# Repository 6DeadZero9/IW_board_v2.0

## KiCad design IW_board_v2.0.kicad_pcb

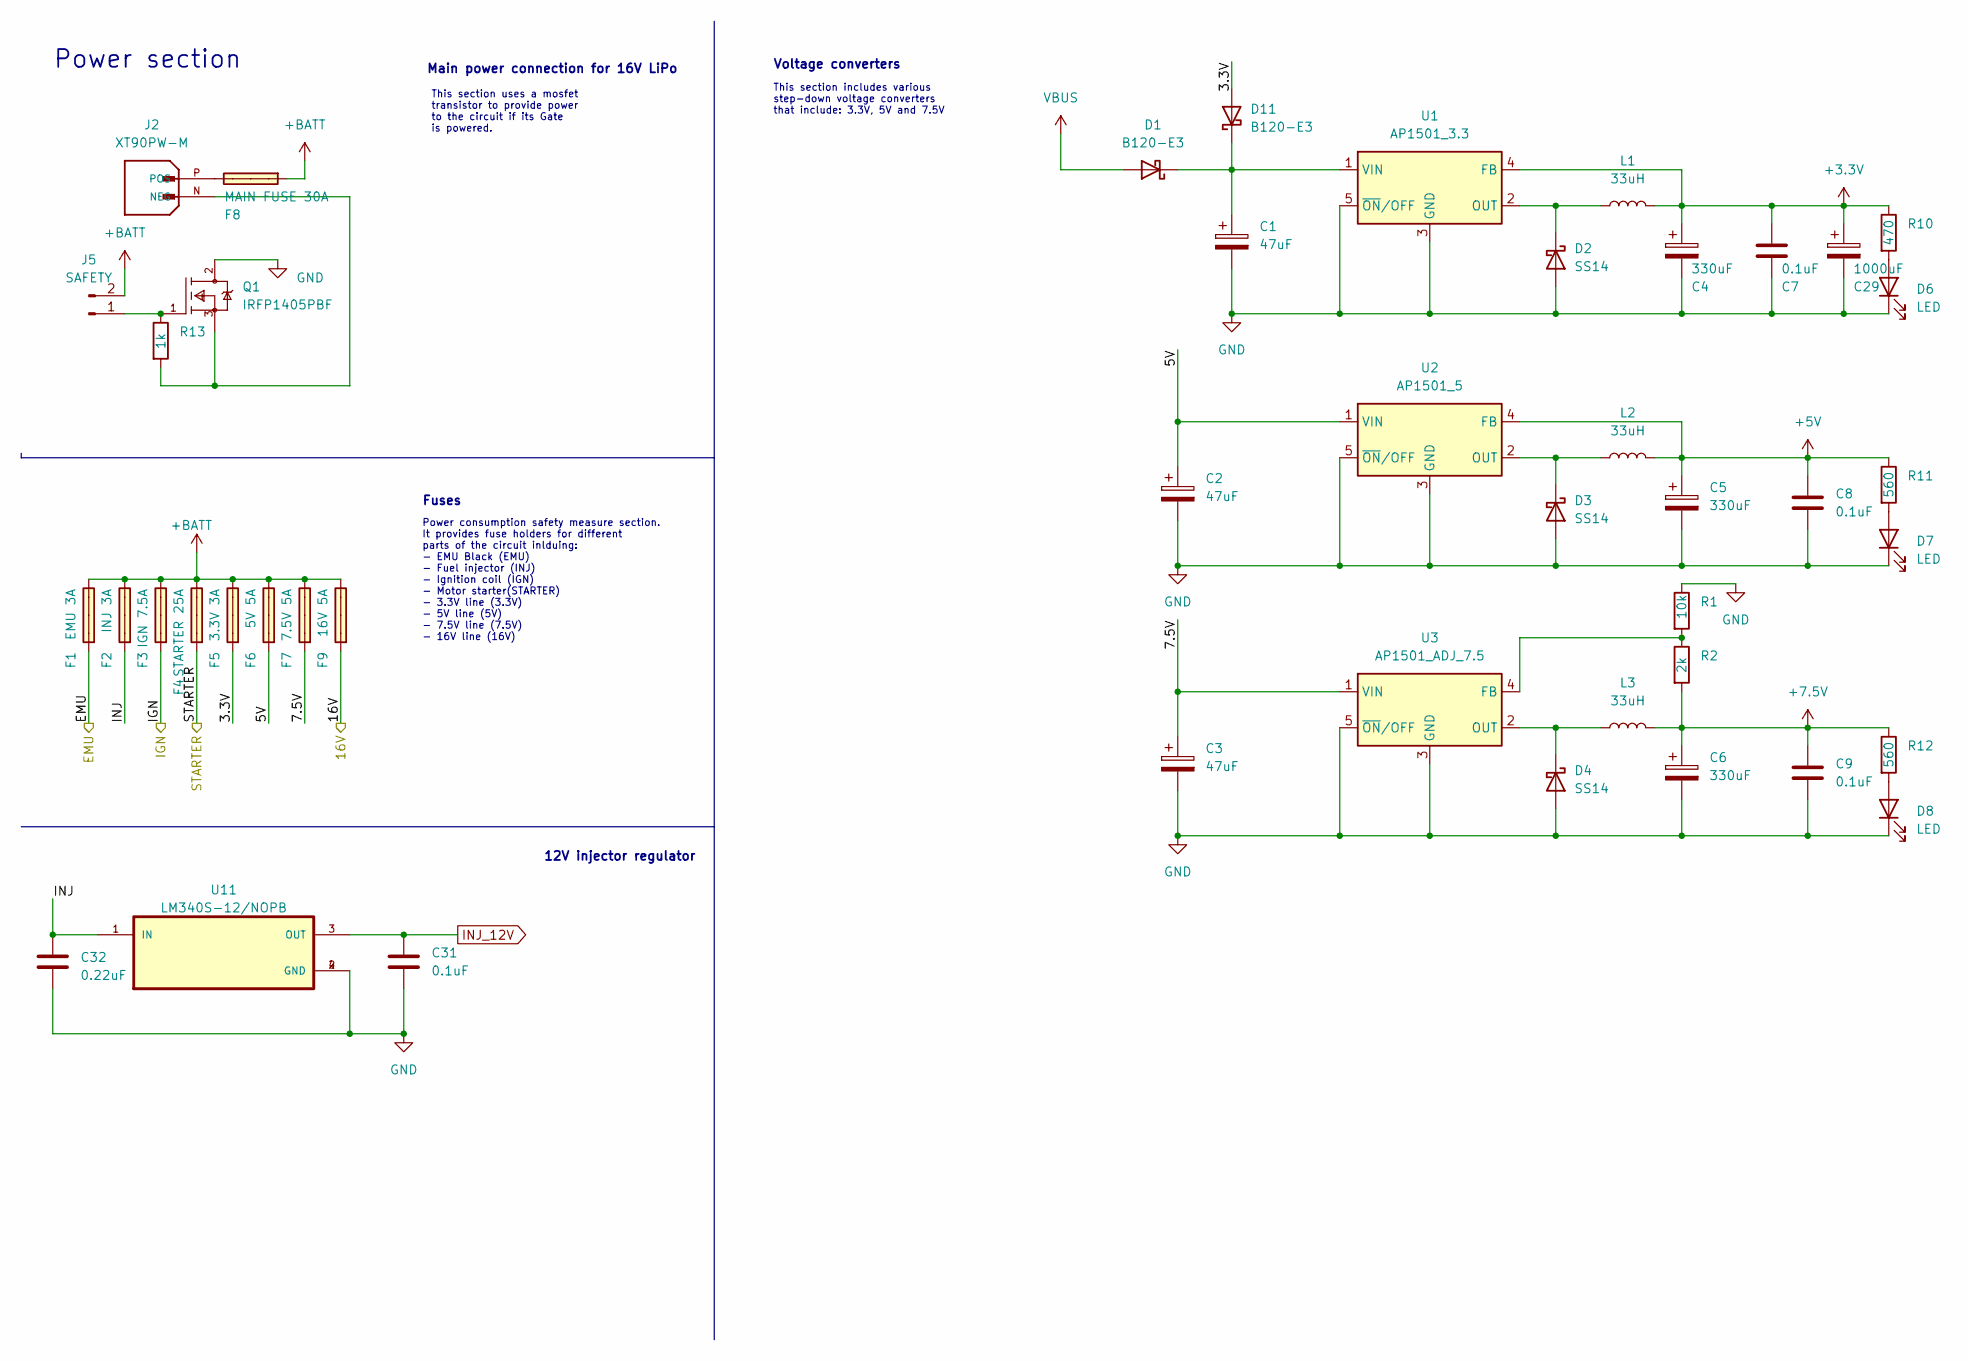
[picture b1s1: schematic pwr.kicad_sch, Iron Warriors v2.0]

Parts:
C1, C2, C3: 47uF; CP_Elec_6.3x5.8
C4, C5, C6: 330uF; CP_Elec_10x10
C7, C8, C9, C31: 0.1uF; C_0603_1608Metric
C29: 1000uF; CP_Radial_D10.0mm_P7.50mm
C32: 0.22uF; C_0603_1608Metric
D1, D11: B120-E3; D_SMA
D2, D3, D4: SS14; D_SMA
D6, D7, D8: LED; LED_0603_1608Metric
F1: EMU 3A; FUSE_3557-2
F2: INJ 3A; FUSE_3557-2
F3: IGN 7.5A; FUSE_3557-2
F4: STARTER 25A; FUSE_3557-2
F5: 3.3V 3A; FUSE_3557-2
F6: 5V 5A; FUSE_3557-2
F7: 7.5V 5A; FUSE_3557-2
F8: MAIN FUSE 30A; FUSE_3557-2
F9: 16V 5A; FUSE_3557-2
J2: XT90PW-M; AMASS_XT90PW-M
J5: SAFETY; TerminalBlock_Phoenix_MPT-0,5-2-2.54_1x02_P2.54mm_Horizontal
L1, L2, L3: 33uH; L_Bourns_SRR1208_12.7x12.7mm
Q1: IRFP1405PBF; TO247AC; mouser part number 942-IRFP1405PBF; digikey description MOSFET N-CH 55V 95A TO247AC
R1: 10k; R_0603_1608Metric
R2: 2k; R_0603_1608Metric
R10: 470; R_0603_1608Metric
R11, R12: 560; R_0603_1608Metric
R13: 1k; R_0603_1608Metric
U1: AP1501_3.3; TO-263-5_TabPin3
U2: AP1501_5; TO-263-5_TabPin3
U3: AP1501_ADJ_7.5; TO-263-5_TabPin3
U11: LM340S-12/NOPB; TO254P1524X483-4N

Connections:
+3.3V: C4.1, C7.1, C29.1, L1.2, R10.1, U1.4 (FB); also elsewhere on the board
+5V: C5.1, C8.1, L2.2, R11.1, U2.4 (FB); also elsewhere on the board
+7.5V: C6.1, C9.1, L3.2, R2.2, R12.1; also elsewhere on the board
+BATT: F1.3, F2.3, F3.3, F4.3, F5.3, F6.3, F7.3, F8.1, F9.3, J5.2
/IO/EMU: F1.1; also elsewhere on the board
/IO/IGN: F3.1; also elsewhere on the board
/IO/STARTER: F4.1; also elsewhere on the board
/PWR/3.3V: D11.2 (A), F5.1
/PWR/5V: C2.1, F6.1, U2.1 (VIN)
/PWR/7.5V: C3.1, F7.1, U3.1 (VIN)
/PWR/16V: F9.1; also elsewhere on the board
/PWR/INJ: C32.1, F2.1, U11.1 (IN)
GND: C1.2, C2.2, C3.2, C4.2, C5.2, C6.2, C7.2, C8.2, C9.2, C29.2, C31.2, C32.2, D2.2 (A), D3.2 (A), D4.2 (A), D6.1 (K), D7.1 (K), D8.1 (K), Q1.2 (D), R1.1, U1.3 (GND), U1.5 (~ON/OFF), U2.3 (GND), U2.5 (~ON/OFF), U3.3 (GND), U3.5 (~ON/OFF), U11.2 (GND), U11.4 (GND); also elsewhere on the board
INJ_12V: C31.1, U11.3 (OUT); also elsewhere on the board
unnamed: C1.1, D1.1 (K), D11.1 (K), U1.1 (VIN)
unnamed: D2.1 (K), L1.1, U1.2 (OUT)
unnamed: D3.1 (K), L2.1, U2.2 (OUT)
unnamed: D4.1 (K), L3.1, U3.2 (OUT)
unnamed: D6.2 (A), R10.2
unnamed: D7.2 (A), R11.2
unnamed: D8.2 (A), R12.2
unnamed: J2.N (NEG), Q1.3 (S), R13.2
unnamed: F8.3, J2.P (POS)
unnamed: J5.1, Q1.1 (G), R13.1
unnamed: R1.2, R2.1, U3.4 (FB)
VBUS: D1.2 (A); also elsewhere on the board

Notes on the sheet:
This section includes various step-down voltage converters that include: 3.3V, 5V and 7.5V
Power consumption safety measure section. It provides fuse holders for different parts of the circuit inlduing: - EMU Black (EMU) - Fuel injector (INJ) - Ignition coil (IGN) - Motor starter(STARTER) - 3.3V line (3.3V) - 5V line (5V) - 7.5V line (7.5V) - 16V line (16V)
This section uses a mosfet transistor to provide power to the circuit if its Gate is powered.
Power section
12V injector regulator
Main power connection for 16V LiPo
Fuses
Voltage converters

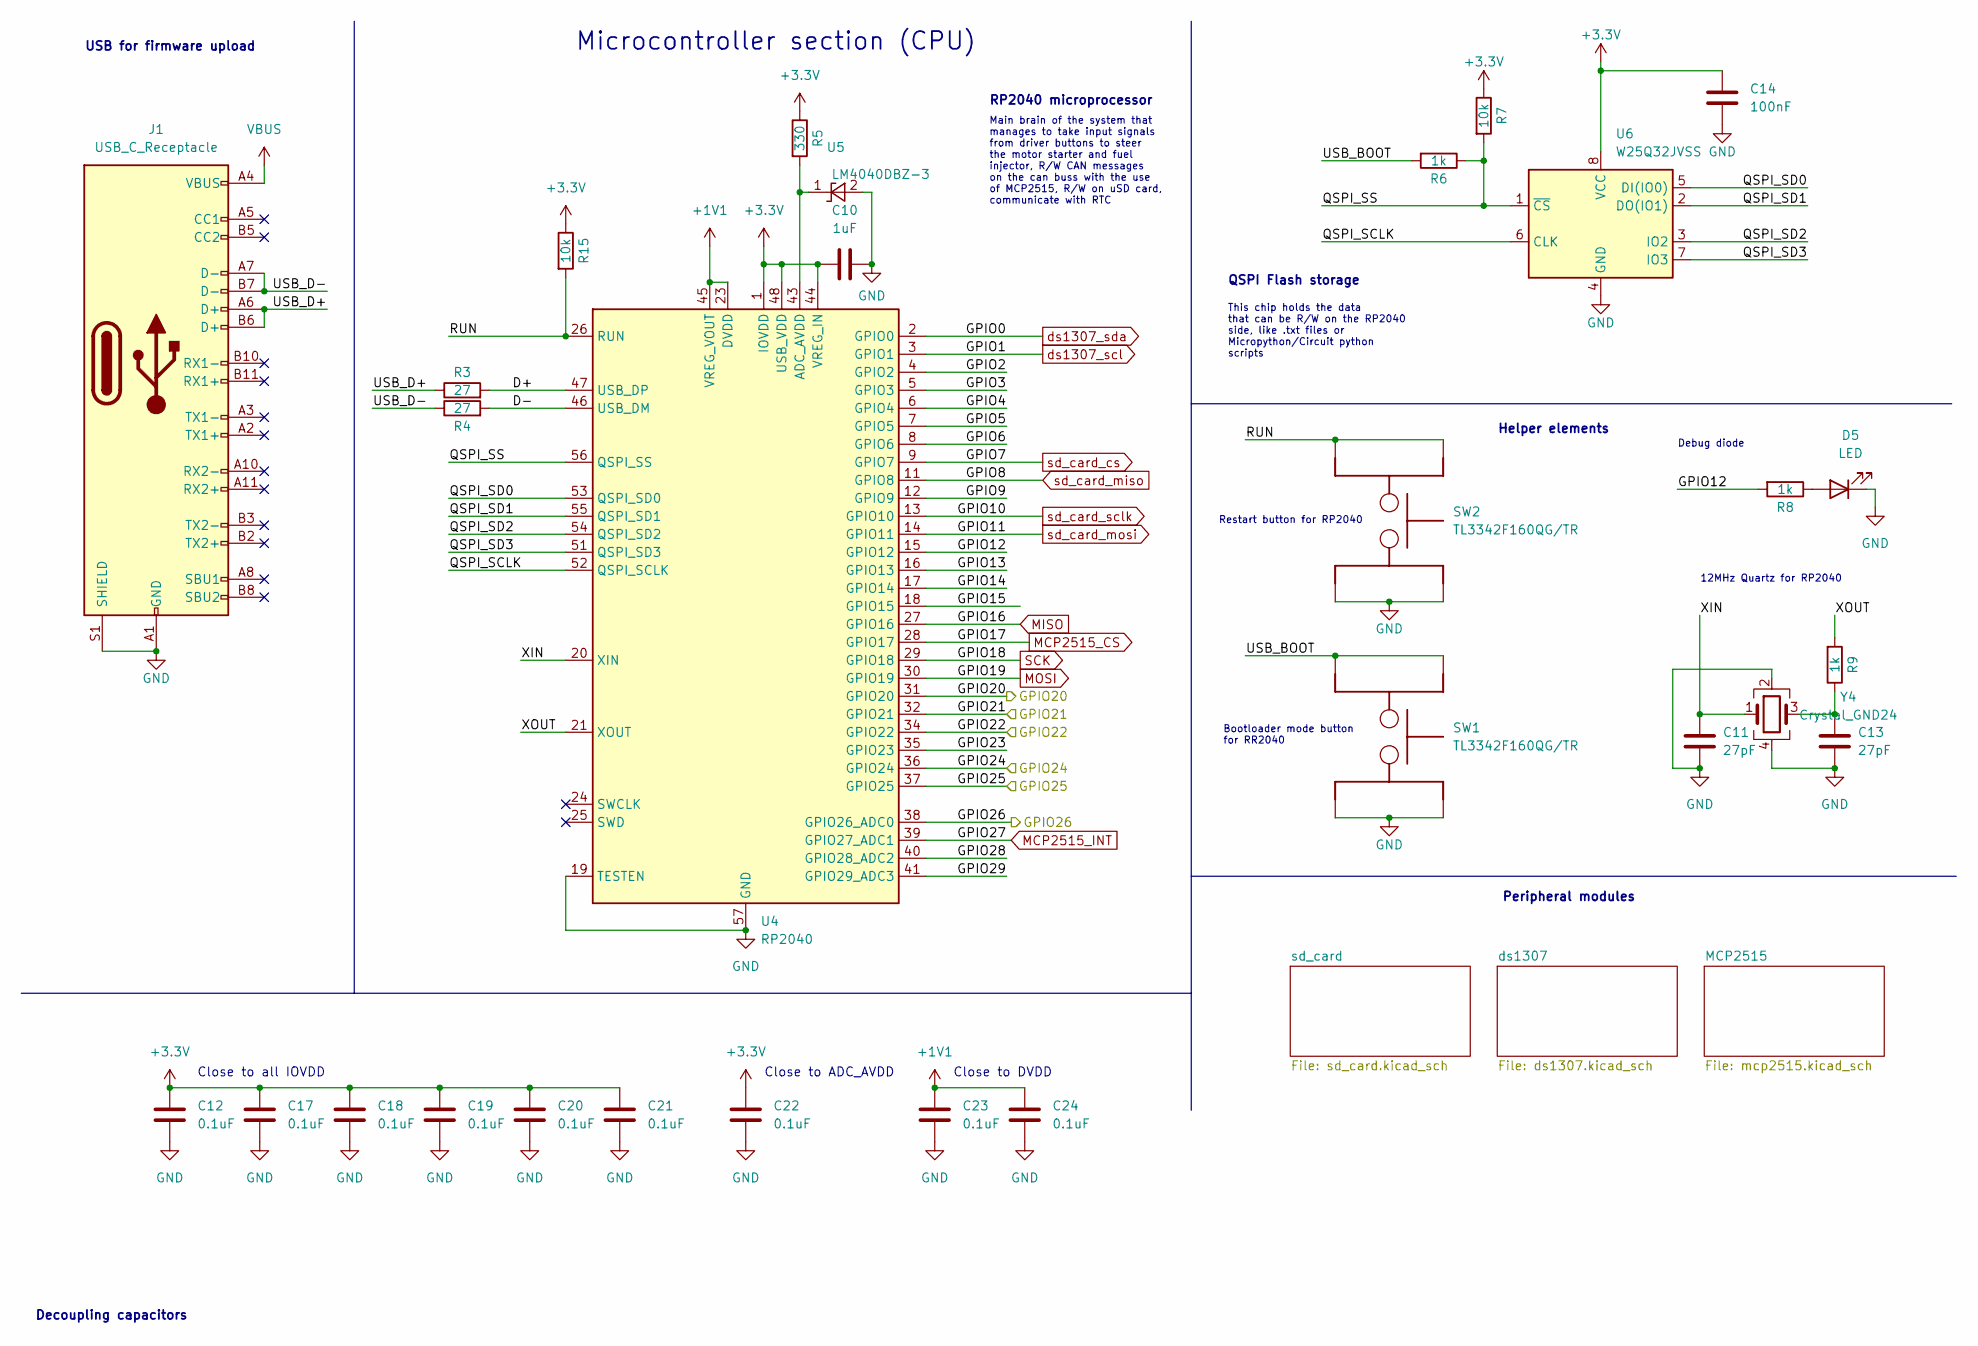
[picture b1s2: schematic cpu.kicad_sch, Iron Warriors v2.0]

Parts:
C10: 1uF; C_0603_1608Metric
C11, C13: 27pF; C_0603_1608Metric
C12, C17, C18, C19, C20, C21, C22, C23, C24: 0.1uF; C_0603_1608Metric
C14: 100nF; C_0603_1608Metric
D5: LED; LED_0603_1608Metric
J1: USB_C_Receptacle; USB_C_Receptacle_HRO_TYPE-C-31-M-12
R3, R4: 27; R_0603_1608Metric
R5: 330; R_0603_1608Metric
R6, R8, R9: 1k; R_0603_1608Metric
R7, R15: 10k; R_0603_1608Metric
SW1, SW2: TL3342F160QG/TR; SW_TL3342F160QG%2fTR
U4: RP2040; QFN-56-1EP_7x7mm_P0.4mm_EP3.2x3.2mm
U5: LM4040DBZ-3; SOT-23
U6: W25Q32JVSS; SOIC-8_5.23x5.23mm_P1.27mm
Y4: Crystal_GND24

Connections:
+1V1: C23.1, C24.1, U4.23 (DVDD), U4.45 (VREG_VOUT), U4.50 (DVDD)
+3.3V: C10.2, C12.1, C14.1, C17.1, C18.1, C19.1, C20.1, C21.1, C22.1, R5.1, R7.1, R15.1, U4.1 (IOVDD), U4.10 (IOVDD), U4.22 (IOVDD), U4.33 (IOVDD), U4.42 (IOVDD), U4.44 (VREG_IN), U4.48 (USB_VDD), U4.49 (IOVDD), U6.8 (VCC); also elsewhere on the board
/CPU/D+: R3.2, U4.47 (USB_DP)
/CPU/D-: R4.2, U4.46 (USB_DM)
/CPU/GPIO2: U4.4 (GPIO2)
/CPU/GPIO3: U4.5 (GPIO3)
/CPU/GPIO4: U4.6 (GPIO4)
/CPU/GPIO5: U4.7 (GPIO5)
/CPU/GPIO6: U4.8 (GPIO6)
/CPU/GPIO9: U4.12 (GPIO9)
/CPU/GPIO12: R8.2, U4.15 (GPIO12)
/CPU/GPIO13: U4.16 (GPIO13)
/CPU/GPIO14: U4.17 (GPIO14)
/CPU/GPIO15: U4.18 (GPIO15)
/CPU/GPIO20: U4.31 (GPIO20); also elsewhere on the board
/CPU/GPIO21: U4.32 (GPIO21); also elsewhere on the board
/CPU/GPIO22: U4.34 (GPIO22); also elsewhere on the board
/CPU/GPIO23: U4.35 (GPIO23)
/CPU/GPIO24: U4.36 (GPIO24); also elsewhere on the board
/CPU/GPIO25: U4.37 (GPIO25); also elsewhere on the board
/CPU/GPIO26: U4.38 (GPIO26_ADC0); also elsewhere on the board
/CPU/GPIO28: U4.40 (GPIO28_ADC2)
/CPU/GPIO29: U4.41 (GPIO29_ADC3)
/CPU/QSPI_SCLK: U4.52 (QSPI_SCLK), U6.6 (CLK)
/CPU/QSPI_SD0: U4.53 (QSPI_SD0), U6.5 (DI(IO0))
/CPU/QSPI_SD1: U4.55 (QSPI_SD1), U6.2 (DO(IO1))
/CPU/QSPI_SD2: U4.54 (QSPI_SD2), U6.3 (IO2)
/CPU/QSPI_SD3: U4.51 (QSPI_SD3), U6.7 (IO3)
/CPU/QSPI_SS: R6.1, R7.2, U4.56 (QSPI_SS), U6.1 (~CS)
/CPU/RUN: R15.2, SW2.3, SW2.4, U4.26 (RUN)
/CPU/USB_BOOT: R6.2, SW1.3, SW1.4
/CPU/USB_D+: J1.A6 (D+), J1.B6 (D+), R3.1
/CPU/USB_D-: J1.A7 (D-), J1.B7 (D-), R4.1
/CPU/XOUT: R9.2, U4.21 (XOUT)
GND: C10.1, C11.2, C12.2, C13.2, C14.2, C17.2, C18.2, C19.2, C20.2, C21.2, C22.2, C23.2, C24.2, D5.1 (K), J1.A1 (GND), J1.A12 (GND), J1.B1 (GND), J1.B12 (GND), J1.S1 (SHIELD), SW1.1, SW1.2, SW2.1, SW2.2, U4.19 (TESTEN), U4.57 (GND), U5.2 (A), U6.4 (GND), Y4.2, Y4.4; also elsewhere on the board
MCP2515_CS: U4.28 (GPIO17); also elsewhere on the board
MCP2515_INT: U4.39 (GPIO27_ADC1); also elsewhere on the board
MISO: U4.27 (GPIO16); also elsewhere on the board
MOSI: U4.30 (GPIO19); also elsewhere on the board
unnamed: D5.2 (A), R8.1
unnamed: R5.2, U4.43 (ADC_AVDD), U5.1 (K)
SCK: U4.29 (GPIO18); also elsewhere on the board
VBUS: J1.A4 (VBUS), J1.A9 (VBUS), J1.B4 (VBUS), J1.B9 (VBUS); also elsewhere on the board
ds1307_scl: U4.3 (GPIO1); also elsewhere on the board
ds1307_sda: U4.2 (GPIO0); also elsewhere on the board
sd_card_cs: U4.9 (GPIO7); also elsewhere on the board
sd_card_miso: U4.11 (GPIO8); also elsewhere on the board
sd_card_mosi: U4.14 (GPIO11); also elsewhere on the board
sd_card_sclk: U4.13 (GPIO10); also elsewhere on the board

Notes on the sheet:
Peripheral modules
Bootloader mode button for RR2040
RP2040 microprocessor
This chip holds the data that can be R/W on the RP2040 side, like .txt files or Micropython/Circuit python scripts
Close to DVDD
Close to all IOVDD
Close to ADC_AVDD
Debug diode
Decoupling capacitors
Restart button for RP2040
USB for firmware upload
Microcontroller section (CPU)
Helper elements
QSPI Flash storage
Main brain of the system that manages to take input signals from driver buttons to steer the motor starter and fuel injector, R/W CAN messages on the can buss with the use of MCP2515, R/W on uSD card, communicate with RTC
12MHz Quartz for RP2040

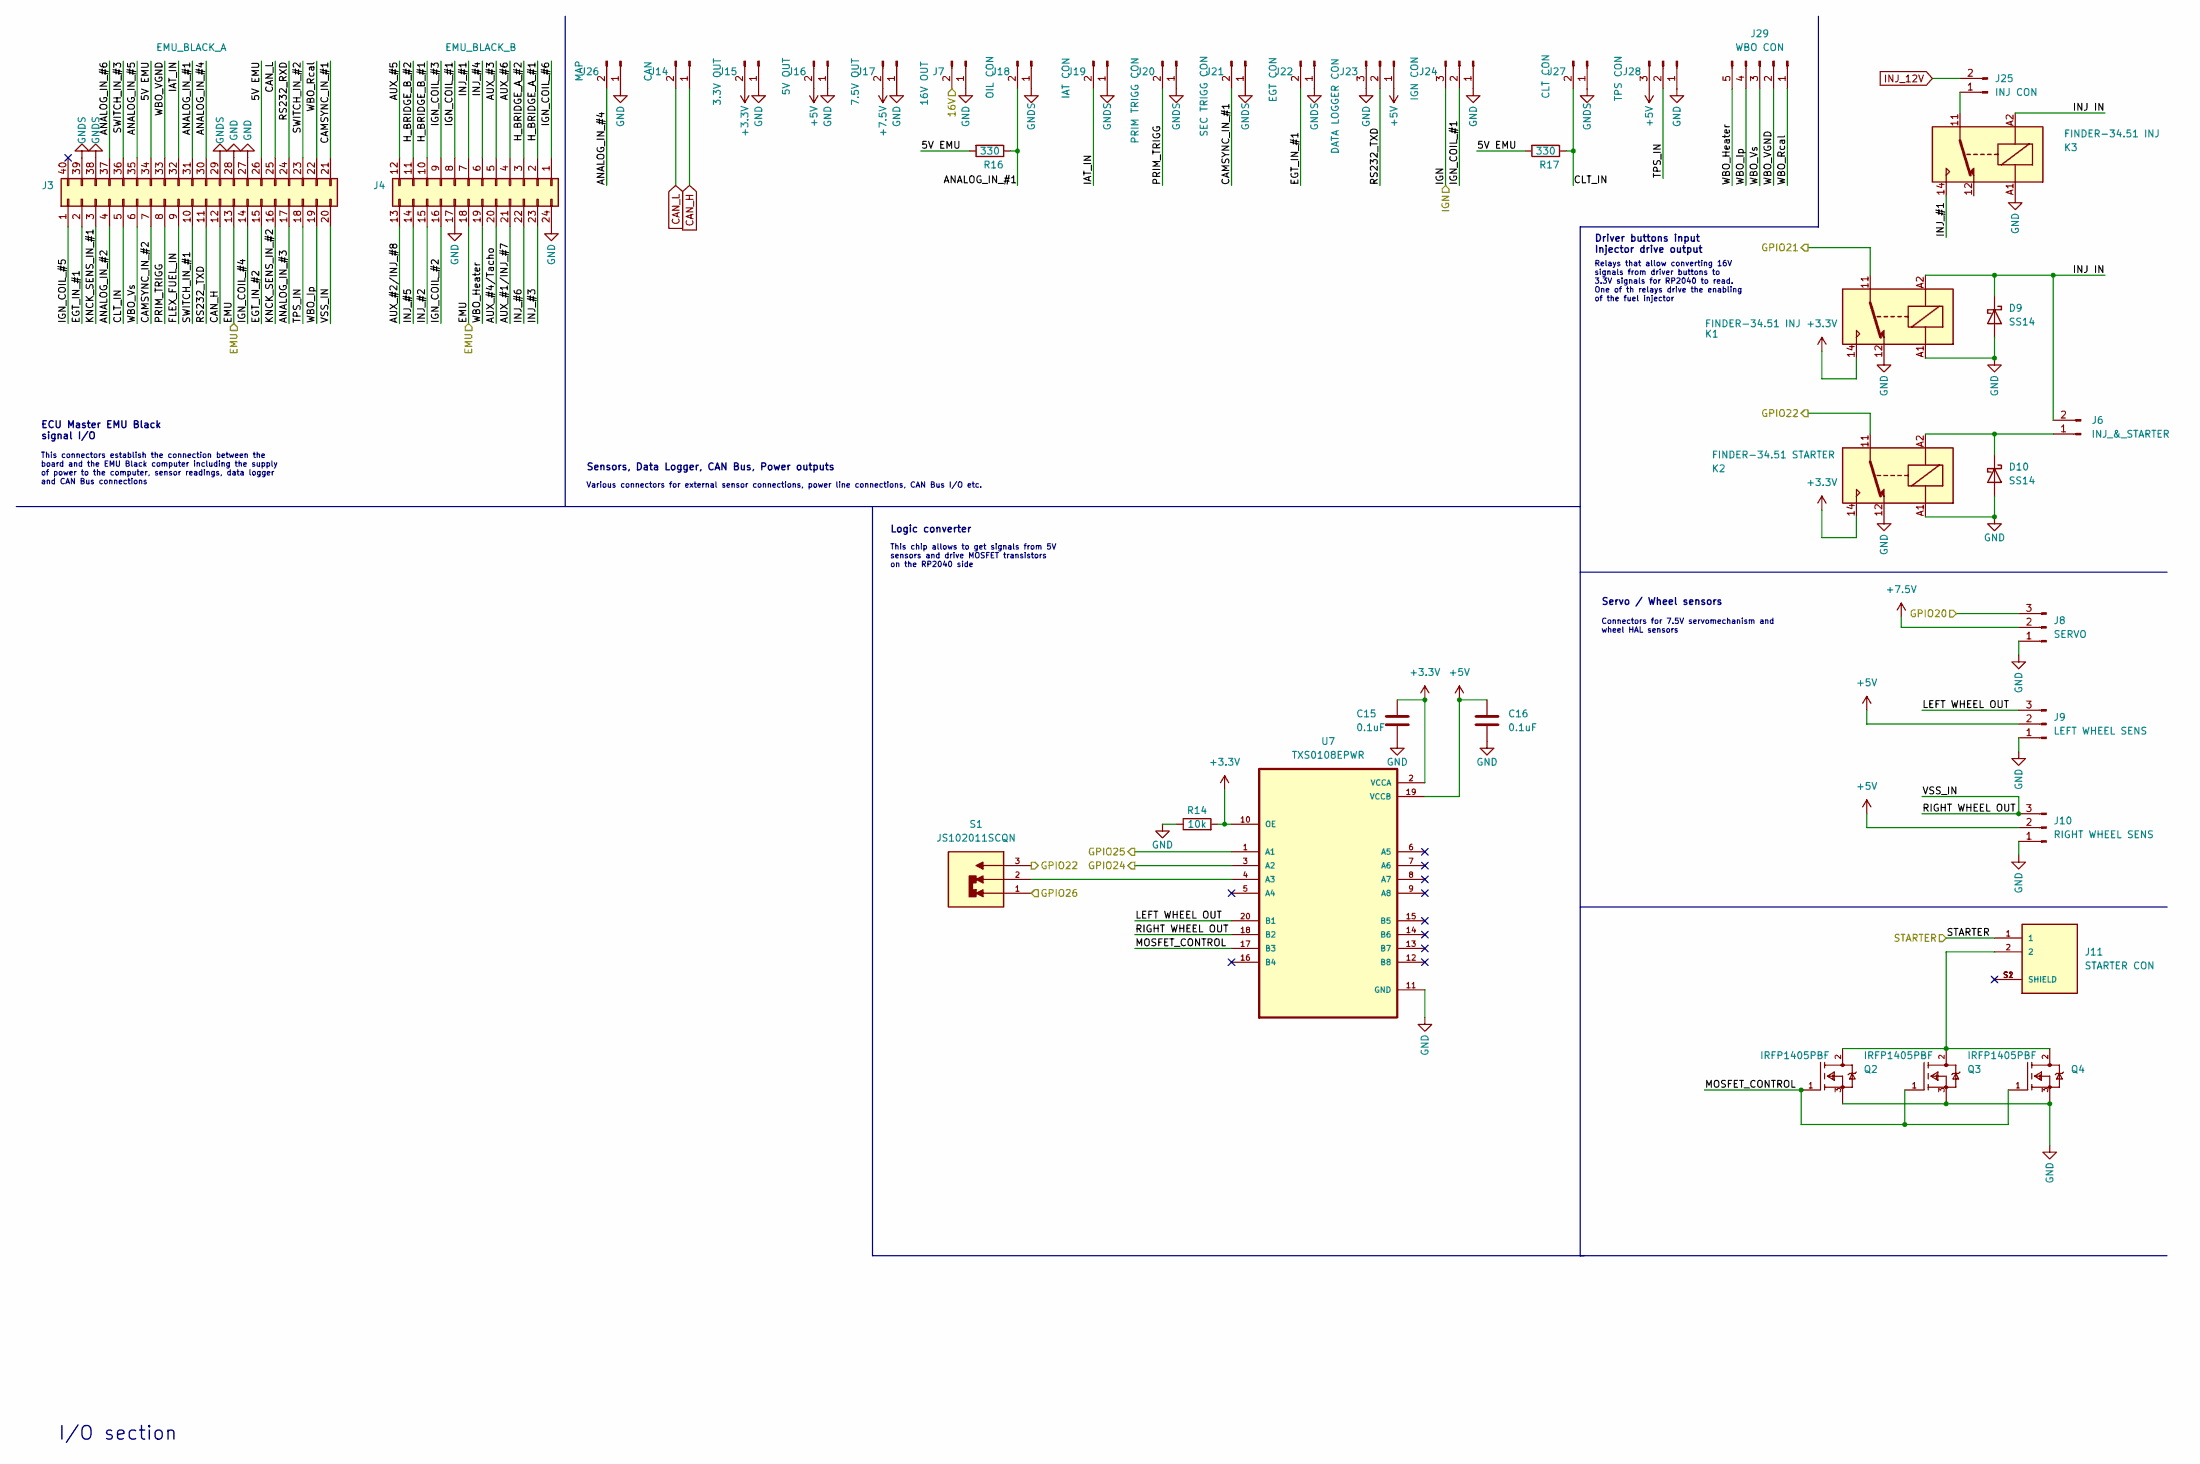
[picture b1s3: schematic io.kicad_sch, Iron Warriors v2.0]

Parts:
C15, C16: 0.1uF; C_0603_1608Metric
D9, D10: SS14; D_SMA
J3: EMU_BLACK_A; IDC-Header_2x20_P2.54mm_Vertical
J4: EMU_BLACK_B; IDC-Header_2x12_P2.54mm_Vertical
J6: INJ_&_STARTER; TerminalBlock_Phoenix_MPT-0,5-2-2.54_1x02_P2.54mm_Horizontal
J7: 16V OUT; TerminalBlock_Phoenix_MPT-0,5-2-2.54_1x02_P2.54mm_Horizontal
J8: SERVO; TerminalBlock_Phoenix_MPT-0,5-3-2.54_1x03_P2.54mm_Horizontal
J9: LEFT WHEEL SENS; TerminalBlock_Phoenix_MPT-0,5-3-2.54_1x03_P2.54mm_Horizontal
J10: RIGHT WHEEL SENS; TerminalBlock_Phoenix_MPT-0,5-3-2.54_1x03_P2.54mm_Horizontal
J11: STARTER CON; AMASS_XT60PW-F
J14: CAN; TerminalBlock_Phoenix_MPT-0,5-2-2.54_1x02_P2.54mm_Horizontal
J15: 3.3V OUT; TerminalBlock_Phoenix_MPT-0,5-2-2.54_1x02_P2.54mm_Horizontal
J16: 5V OUT; TerminalBlock_Phoenix_MPT-0,5-2-2.54_1x02_P2.54mm_Horizontal
J17: 7.5V OUT; TerminalBlock_Phoenix_MPT-0,5-2-2.54_1x02_P2.54mm_Horizontal
J18: OIL CON; TerminalBlock_Phoenix_MPT-0,5-2-2.54_1x02_P2.54mm_Horizontal
J19: IAT CON; TerminalBlock_Phoenix_MPT-0,5-2-2.54_1x02_P2.54mm_Horizontal
J20: PRIM TRIGG CON; TerminalBlock_Phoenix_MPT-0,5-2-2.54_1x02_P2.54mm_Horizontal
J21: SEC TRIGG CON; TerminalBlock_Phoenix_MPT-0,5-2-2.54_1x02_P2.54mm_Horizontal
J22: EGT CON; TerminalBlock_Phoenix_MPT-0,5-2-2.54_1x02_P2.54mm_Horizontal
J23: DATA LOGGER CON; TerminalBlock_Phoenix_MPT-0,5-3-2.54_1x03_P2.54mm_Horizontal
J24: IGN CON; TerminalBlock_Phoenix_MPT-0,5-3-2.54_1x03_P2.54mm_Horizontal
J25: INJ CON; TerminalBlock_Phoenix_MPT-0,5-2-2.54_1x02_P2.54mm_Horizontal
J26: MAP; TerminalBlock_Phoenix_MPT-0,5-2-2.54_1x02_P2.54mm_Horizontal
J27: CLT CON; TerminalBlock_Phoenix_MPT-0,5-2-2.54_1x02_P2.54mm_Horizontal
J28: TPS CON; TerminalBlock_Phoenix_MPT-0,5-3-2.54_1x03_P2.54mm_Horizontal
J29: WBO CON; TerminalBlock_Phoenix_MPT-0,5-5-2.54_1x05_P2.54mm_Horizontal
K1, K3: FINDER-34.51 INJ; Relay_SPDT_Finder_34.51_Vertical
K2: FINDER-34.51 STARTER; Relay_SPDT_Finder_34.51_Vertical
Q2, Q3, Q4: IRFP1405PBF; TO247AC; mouser part number 942-IRFP1405PBF; digikey description MOSFET N-CH 55V 95A TO247AC
R14: 10k; R_0603_1608Metric
R16, R17: 330; R_0603_1608Metric
S1: JS102011SCQN; SW_JS102011SCQN; PARTREV 8 Oct 21
U7: TXS0108EPWR; SOP65P640X120-20N

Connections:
+3.3V: C15.2, J15.2, K1.14, K2.14, R14.2, U7.2 (VCCA), U7.10 (OE); also elsewhere on the board
+5V: C16.2, J9.2, J10.2, J16.2, J23.1, J28.3, U7.19 (VCCB); also elsewhere on the board
+7.5V: J8.2, J17.2; also elsewhere on the board
/CPU/GPIO20: J8.3; also elsewhere on the board
/CPU/GPIO21: K1.11; also elsewhere on the board
/CPU/GPIO22: K2.11, S1.3; also elsewhere on the board
/CPU/GPIO24: U7.3 (A2); also elsewhere on the board
/CPU/GPIO25: U7.1 (A1); also elsewhere on the board
/CPU/GPIO26: S1.1; also elsewhere on the board
/IO/5V EMU: J3.26, J3.34, R16.2, R17.2
/IO/ANALOG_IN_#1: J3.31, J18.2, R16.1
/IO/ANALOG_IN_#2: J3.4
/IO/ANALOG_IN_#3: J3.17
/IO/ANALOG_IN_#4: J3.30, J26.2
/IO/ANALOG_IN_#5: J3.35
/IO/ANALOG_IN_#6: J3.37
/IO/AUX_#1/INJ_#7: J4.21
/IO/AUX_#2/INJ_#8: J4.13
/IO/AUX_#3: J4.5
/IO/AUX_#4/Tacho: J4.20
/IO/AUX_#5: J4.12
/IO/AUX_#6: J4.4
/IO/CAMSYNC_IN_#1: J3.21, J21.2
/IO/CAMSYNC_IN_#2: J3.7
/IO/CLT_IN: J3.5, J27.2, R17.1
/IO/EGT_IN_#1: J3.2, J22.2
/IO/EGT_IN_#2: J3.15
/IO/EMU: J3.13, J4.18; also elsewhere on the board
/IO/FLEX_FUEL_IN: J3.9
/IO/H_BRIDGE_A_#1: J4.2
/IO/H_BRIDGE_A_#2: J4.3
/IO/H_BRIDGE_B_#1: J4.10
/IO/H_BRIDGE_B_#2: J4.11
/IO/IAT_IN: J3.32, J19.2
/IO/IGN: J24.3; also elsewhere on the board
/IO/IGN_COIL_#1: J4.8, J24.2
/IO/IGN_COIL_#2: J4.16
/IO/IGN_COIL_#3: J4.9
/IO/IGN_COIL_#4: J3.14
/IO/IGN_COIL_#5: J3.1
/IO/IGN_COIL_#6: J4.1
/IO/INJ IN: D9.1 (K), J6.2, K1.A2, K3.A2
/IO/INJ_#1: J4.7, K3.14
/IO/INJ_#2: J4.15
/IO/INJ_#3: J4.23
/IO/INJ_#4: J4.6
/IO/INJ_#5: J4.14
/IO/INJ_#6: J4.22
/IO/KNCK_SENS_IN_#1: J3.3
/IO/KNCK_SENS_IN_#2: J3.16
/IO/LEFT WHEEL OUT: J9.3, U7.20 (B1)
/IO/MOSFET_CONTROL: Q2.1 (G), Q3.1 (G), Q4.1 (G), U7.17 (B3)
/IO/PRIM_TRIGG: J3.8, J20.2
/IO/RIGHT WHEEL OUT: J3.20, J10.3, U7.18 (B2)
/IO/RS232_RXD: J3.24
/IO/RS232_TXD: J3.11, J23.2
/IO/STARTER: J11.1; also elsewhere on the board
/IO/SWITCH_IN_#1: J3.10
/IO/SWITCH_IN_#2: J3.23
/IO/SWITCH_IN_#3: J3.36
/IO/TPS_IN: J3.18, J28.2
/IO/WBO_Heater: J4.19, J29.5
/IO/WBO_Ip: J3.19, J29.4
/IO/WBO_Rcal: J3.22, J29.1
/IO/WBO_VGND: J3.33, J29.2
/IO/WBO_Vs: J3.6, J29.3
/PWR/16V: J7.2; also elsewhere on the board
CAN_H: J3.12, J14.1; also elsewhere on the board
CAN_L: J3.25, J14.2; also elsewhere on the board
GND: C15.1, C16.1, D9.2 (A), D10.2 (A), J3.27, J3.28, J4.17, J4.24, J7.1, J8.1, J9.1, J10.1, J15.1, J16.1, J17.1, J23.3, J24.1, J26.1, J28.1, K1.12, K1.A1, K2.12, K2.A1, K3.A1, Q2.3 (S), Q3.3 (S), Q4.3 (S), R14.1, U7.11 (GND); also elsewhere on the board
GNDS: J3.29, J3.38, J3.39, J18.1, J19.1, J20.1, J21.1, J22.1, J27.1
INJ_12V: J25.2; also elsewhere on the board
unnamed: D10.1 (K), J6.1, K2.A2
unnamed: J25.1, K3.11
unnamed: J11.2, Q2.2 (D), Q3.2 (D), Q4.2 (D)
unnamed: S1.2, U7.4 (A3)

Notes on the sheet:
This connectors establish the connection between the board and the EMU Black computer including the supply of power to the computer, sensor readings, data logger and CAN Bus connections
This chip allows to get signals from 5V sensors and drive MOSFET transistors on the RP2040 side
ECU Master EMU Black signal I/O
Servo / Wheel sensors
Connectors for 7.5V servomechanism and wheel HAL sensors
Sensors, Data Logger, CAN Bus, Power outputs
Driver buttons input Injector drive output
Relays that allow converting 16V signals from driver buttons to 3.3V signals for RP2040 to read. One of th relays drive the enabling of the fuel injector
Various connectors for external sensor connections, power line connections, CAN Bus I/O etc.
I/O section
Logic converter

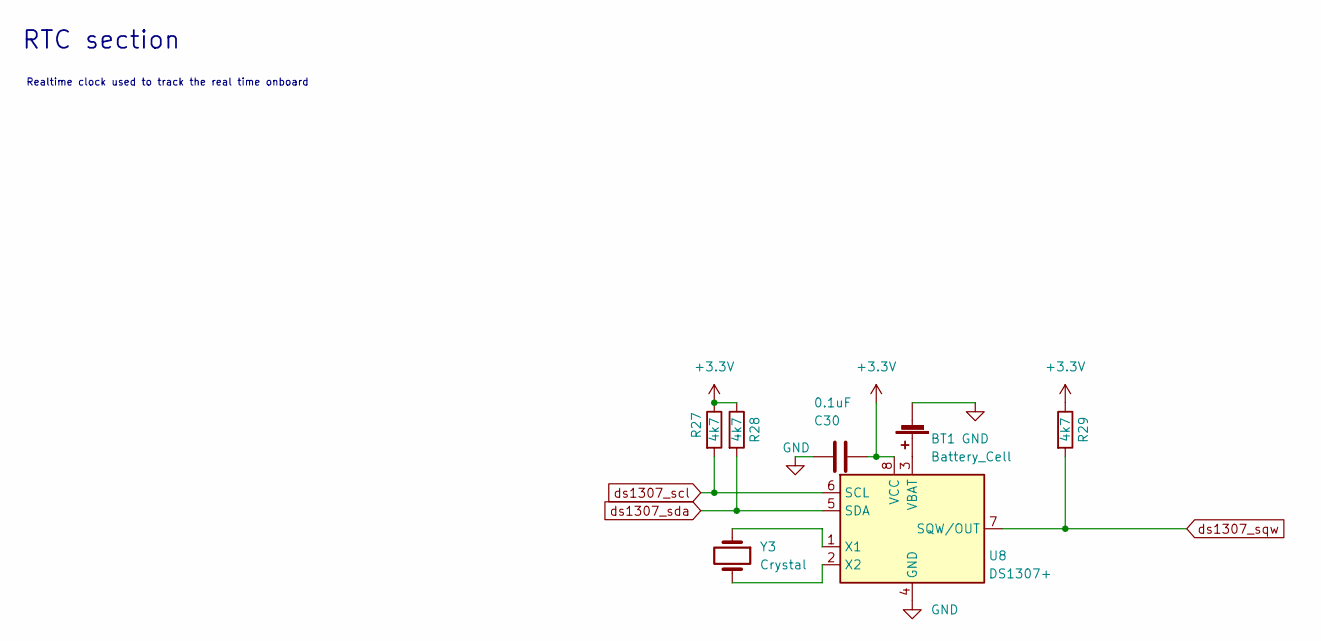
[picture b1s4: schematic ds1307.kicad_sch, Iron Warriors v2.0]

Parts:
BT1: Battery_Cell; BatteryHolder_Keystone_3034_1x20mm
C30: 0.1uF; C_0603_1608Metric
R27, R28, R29: 4k7; R_0603_1608Metric
U8: DS1307+; SOIC-8_3.9x4.9mm_P1.27mm
Y3: Crystal; Crystal_SMD_3215-2Pin_3.2x1.5mm

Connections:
+3.3V: C30.1, R27.1, R28.1, R29.1, U8.8 (VCC); also elsewhere on the board
GND: BT1.2 (-), C30.2, U8.4 (GND); also elsewhere on the board
unnamed: BT1.1 (+), U8.3 (VBAT)
unnamed: U8.1 (X1), Y3.1
unnamed: U8.2 (X2), Y3.2
ds1307_scl: R27.2, U8.6 (SCL); also elsewhere on the board
ds1307_sda: R28.2, U8.5 (SDA); also elsewhere on the board
ds1307_sqw: R29.2, U8.7 (SQW/OUT)

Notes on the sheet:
Realtime clock used to track the real time onboard
RTC section

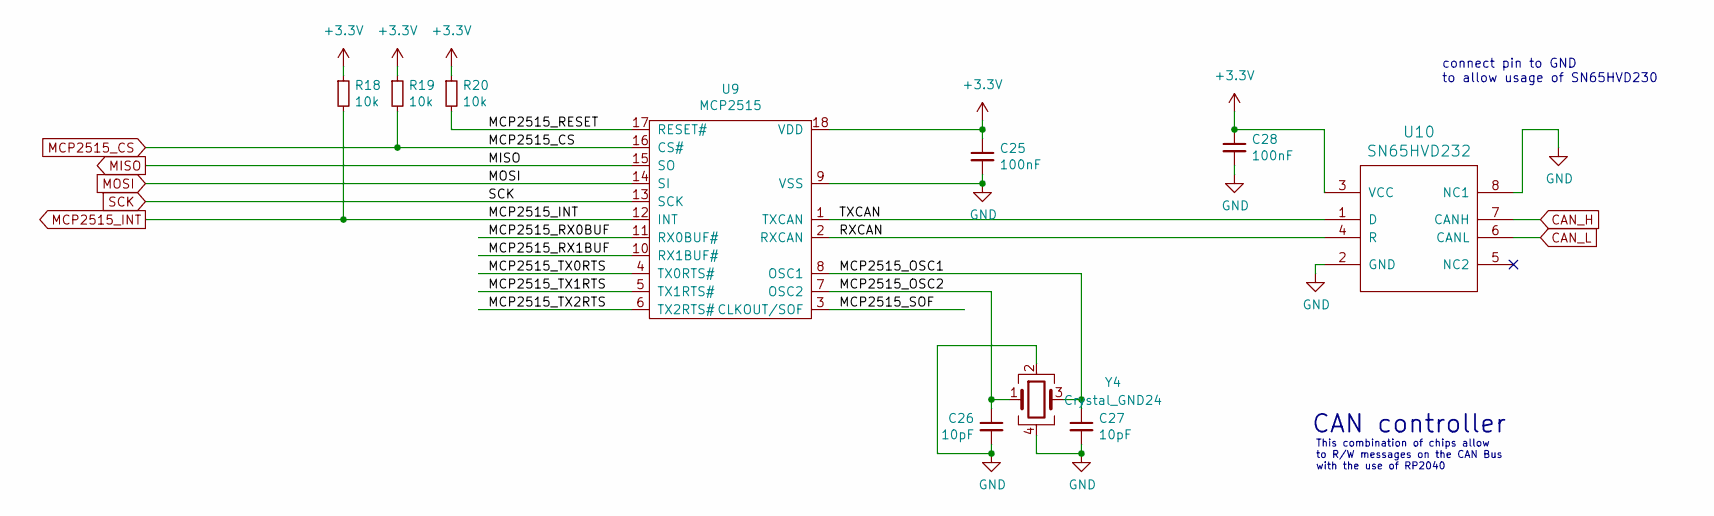
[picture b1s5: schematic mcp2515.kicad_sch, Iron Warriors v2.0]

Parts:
C25, C28: 100nF; C_0603_1608Metric
C26, C27: 10pF; C_0603_1608Metric
R18, R19, R20: 10k; R_0603_1608Metric
U9: MCP2515; SOIC-18W_7.5x11.6mm_P1.27mm
U10: SN65HVD232; SOIC-8_3.9x4.9mm_P1.27mm
Y4: Crystal_GND24

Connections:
+3.3V: C25.1, C28.1, R18.1, R19.1, R20.1, U9.18 (VDD), U10.3 (VCC); also elsewhere on the board
/CPU/MCP2515/MCP2515_RESET: R20.2, U9.17 (RESET#)
/CPU/MCP2515/MCP2515_RX0BUF: U9.11 (RX0BUF#)
/CPU/MCP2515/MCP2515_RX1BUF: U9.10 (RX1BUF#)
/CPU/MCP2515/MCP2515_SOF: U9.3 (CLKOUT/SOF)
/CPU/MCP2515/MCP2515_TX0RTS: U9.4 (TX0RTS#)
/CPU/MCP2515/MCP2515_TX1RTS: U9.5 (TX1RTS#)
/CPU/MCP2515/MCP2515_TX2RTS: U9.6 (TX2RTS#)
/CPU/MCP2515/RXCAN: U9.2 (RXCAN), U10.4 (R)
/CPU/MCP2515/TXCAN: U9.1 (TXCAN), U10.1 (D)
CAN_H: U10.7 (CANH); also elsewhere on the board
CAN_L: U10.6 (CANL); also elsewhere on the board
GND: C25.2, C26.2, C27.2, C28.2, U9.9 (VSS), U10.2 (GND), U10.8 (NC1), Y4.2, Y4.4; also elsewhere on the board
MCP2515_CS: R19.2, U9.16 (CS#); also elsewhere on the board
MCP2515_INT: R18.2, U9.12 (INT); also elsewhere on the board
MISO: U9.15 (SO); also elsewhere on the board
MOSI: U9.14 (SI); also elsewhere on the board
SCK: U9.13 (SCK); also elsewhere on the board

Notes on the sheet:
CAN controller
This combination of chips allow to R/W messages on the CAN Bus with the use of RP2040
connect pin to GND to allow usage of SN65HVD230

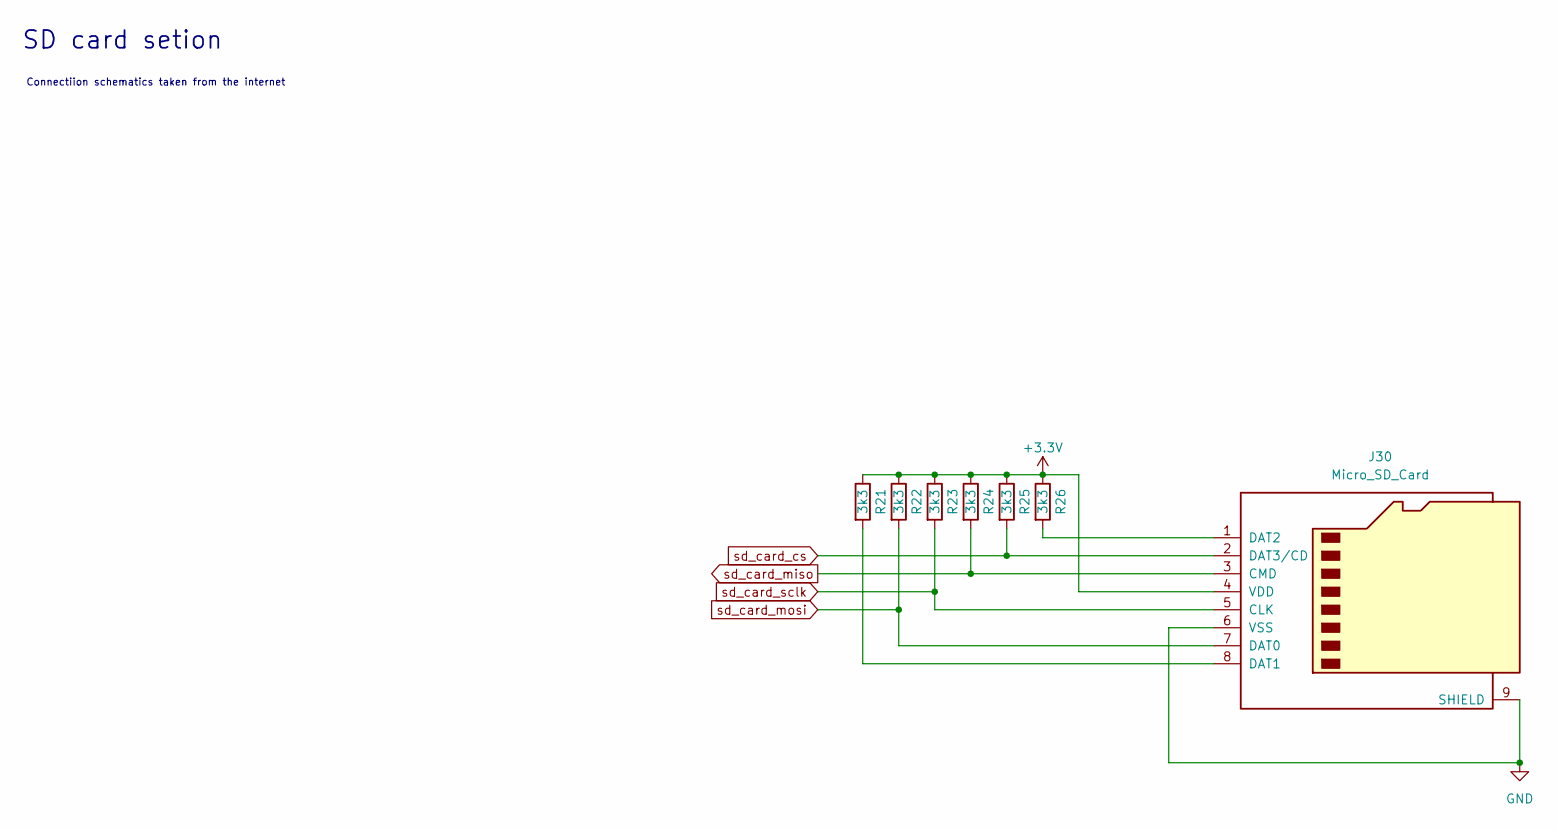
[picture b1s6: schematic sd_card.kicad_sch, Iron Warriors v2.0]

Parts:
J30: Micro_SD_Card; 112J-TDAR-R01
R21, R22, R23, R24, R25, R26: 3k3; R_0603_1608Metric

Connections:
+3.3V: J30.4 (VDD), R21.1, R22.1, R23.1, R24.1, R25.1, R26.1; also elsewhere on the board
GND: J30.6 (VSS), J30.9 (SHIELD); also elsewhere on the board
unnamed: J30.8 (DAT1), R21.2
unnamed: J30.1 (DAT2), R26.2
sd_card_cs: J30.2 (DAT3/CD), R25.2; also elsewhere on the board
sd_card_miso: J30.3 (CMD), R24.2; also elsewhere on the board
sd_card_mosi: J30.7 (DAT0), R22.2; also elsewhere on the board
sd_card_sclk: J30.5 (CLK), R23.2; also elsewhere on the board

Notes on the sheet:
SD card setion
Connectiion schematics taken from the internet

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
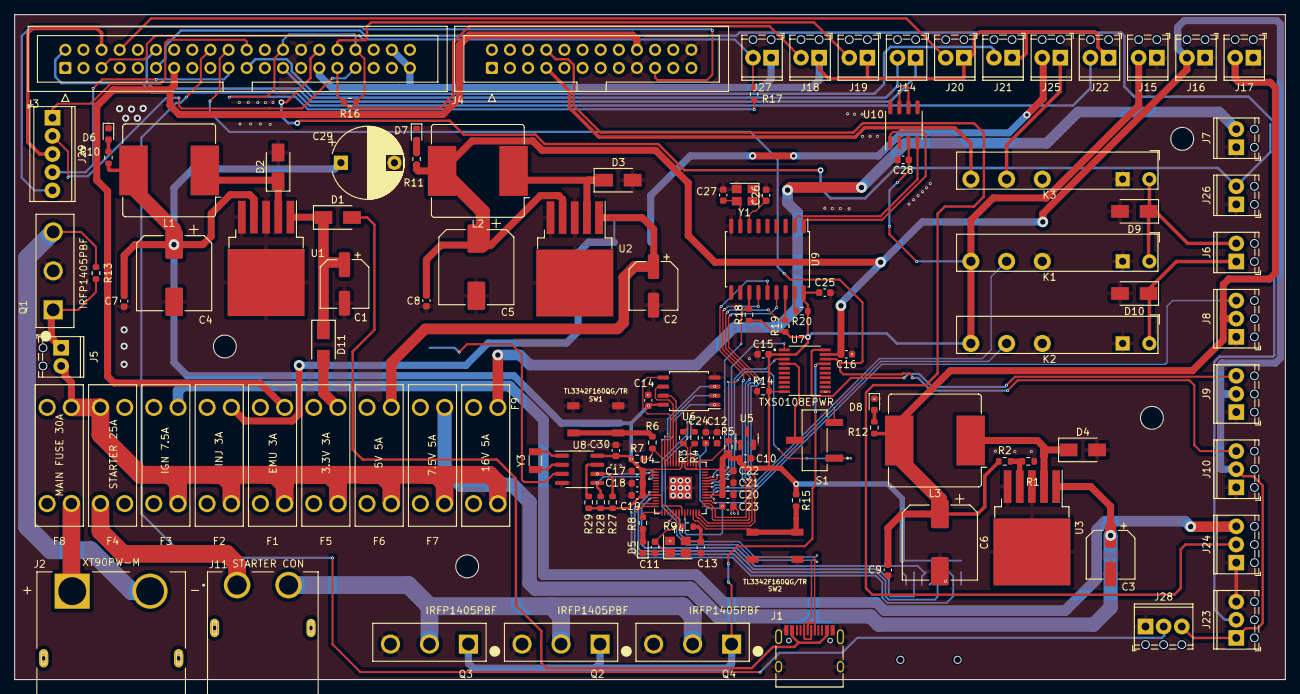
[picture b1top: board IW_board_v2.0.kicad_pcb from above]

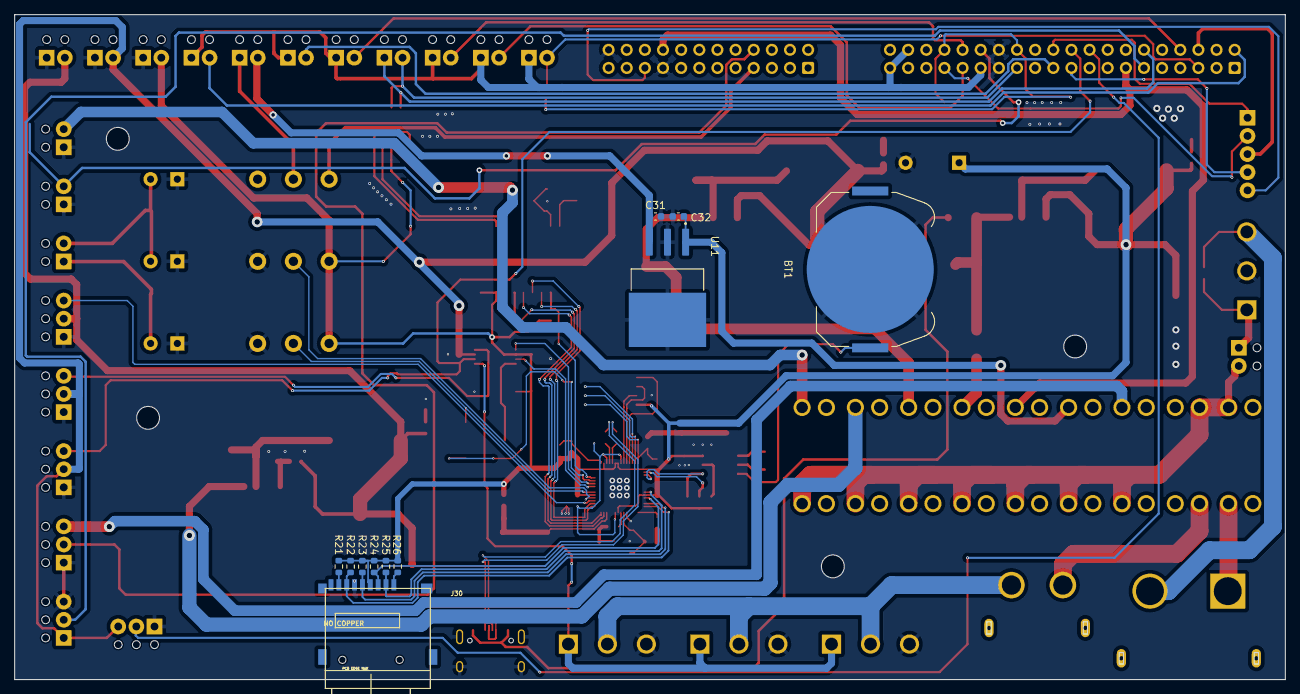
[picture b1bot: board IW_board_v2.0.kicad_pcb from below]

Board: 2 copper layers, 177.9 x 93.1 mm, 137 parts (11 on the bottom side), 101 nets.

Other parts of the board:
Y1: Crystal_GND24; Crystal_SMD_3225-4Pin_3.2x2.5mm

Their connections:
GND: Y1.2, Y1.4; also elsewhere on the board

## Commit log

2022-12-06 Basic schematic edited
2022-12-06 Expanded IO
2022-12-08 Rev 1.0
2022-12-13 Initial PCB view
2023-01-09 First full version of the PCB
2023-04-19 Small corrections
2023-05-02 Added CAN transsiver to RP2040
2023-05-29 Added lambda connection, switching between PWM and 3.3v signal to drive mosfets.
2023-07-26 Added DS1307 RTC and micro SD card
2023-08-01 Added schematic descriptions
2023-08-23 Added 12V regulator for injector
